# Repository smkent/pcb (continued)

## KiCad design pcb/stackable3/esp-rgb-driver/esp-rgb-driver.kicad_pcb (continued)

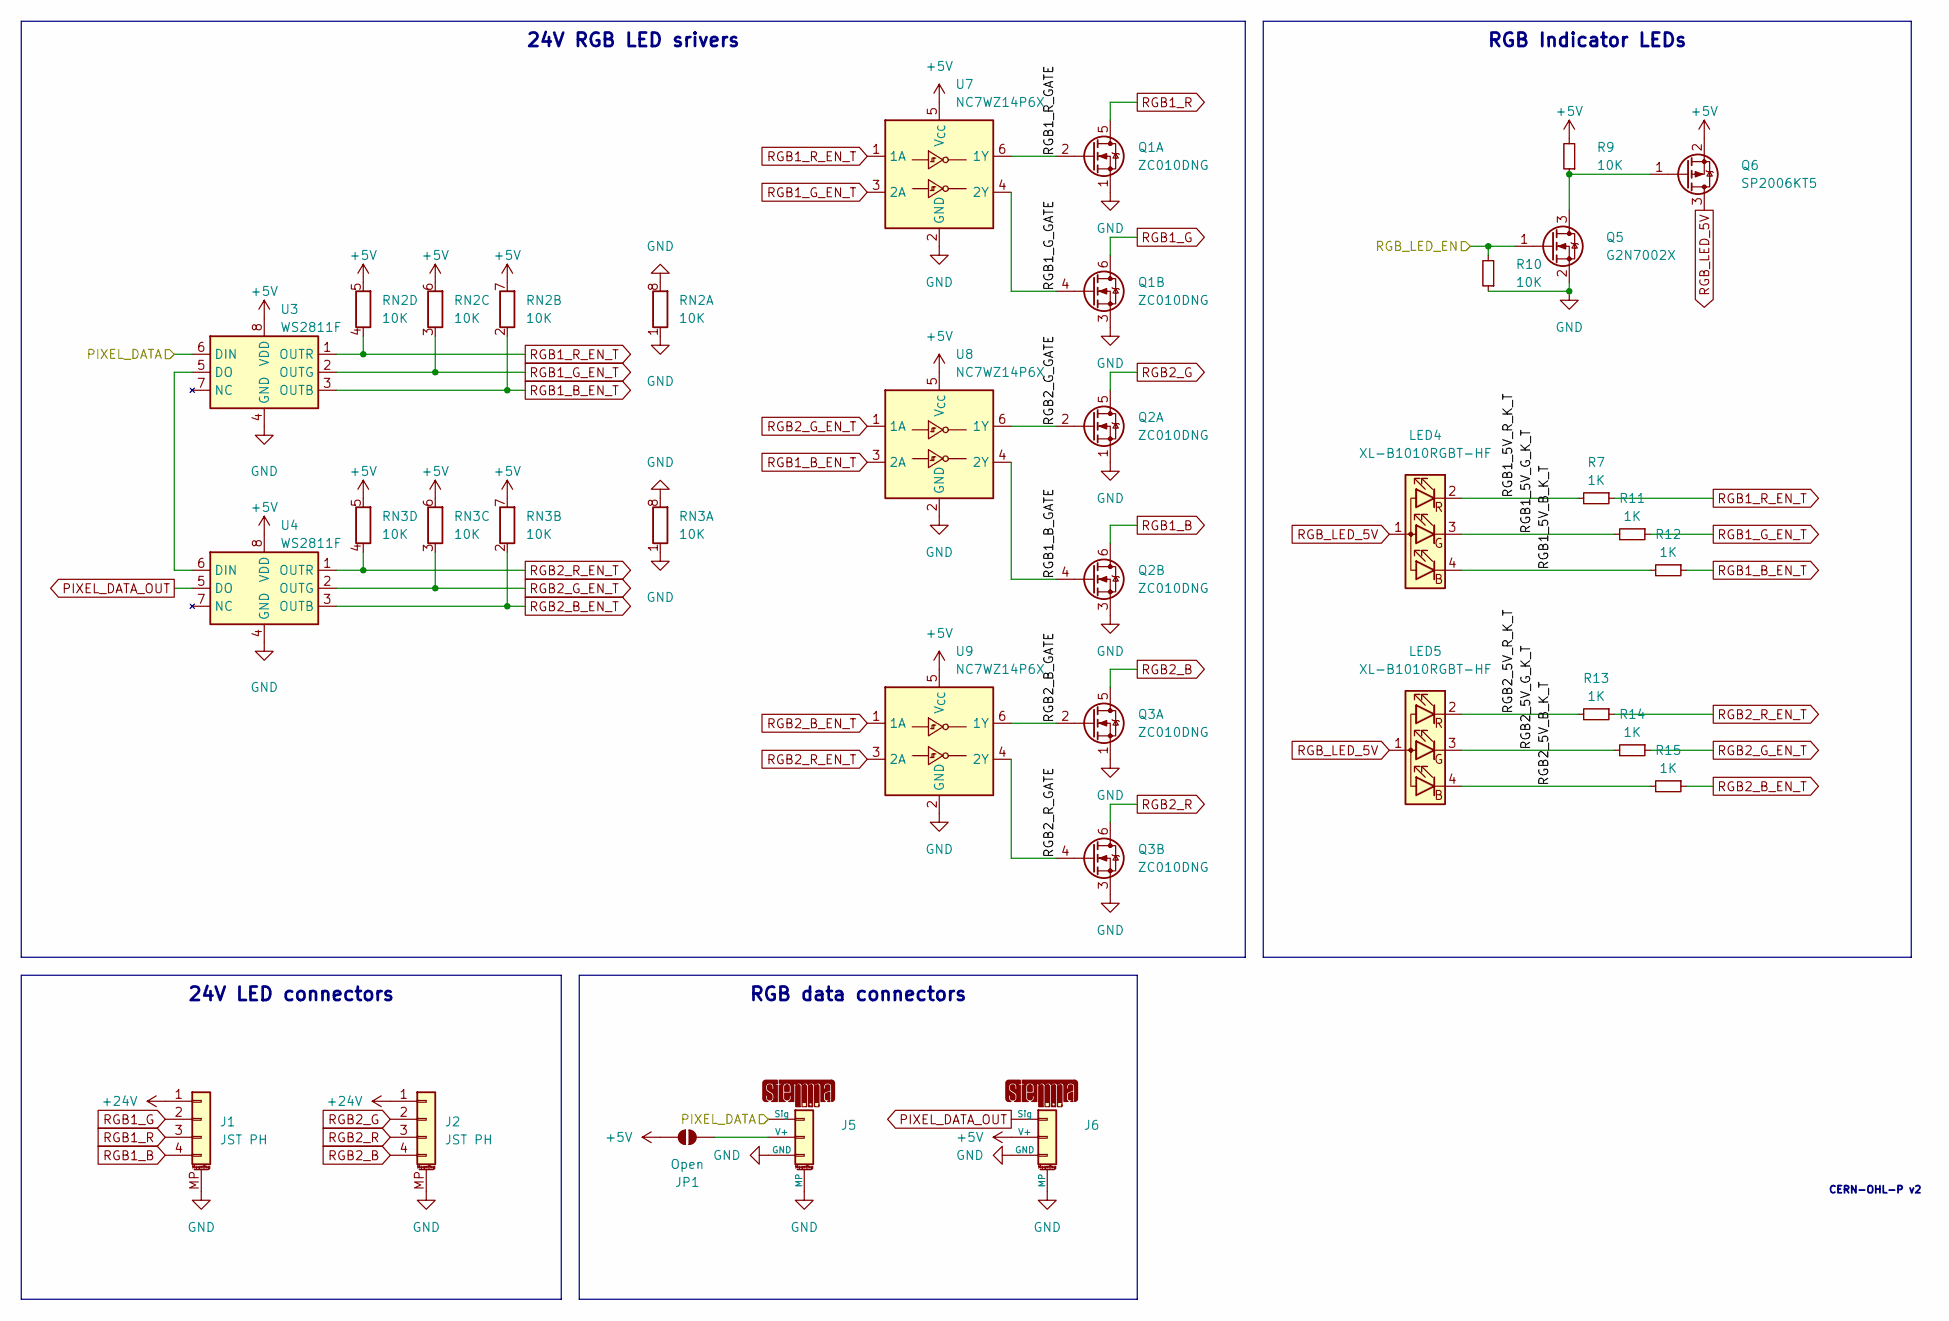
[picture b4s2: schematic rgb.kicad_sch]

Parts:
J1, J2: JST PH; JST_PH_S4B-PH-SM4-TB_1x04-1MP_P2.00mm_Horizontal; LCSC Part C5343396
J5, J6: STEMMA-Signal; STEMMA-Signal-SMD-horizontal; LCSC Part C5372880
JP1: Open; SolderJumper-2_P1.3mm_Open_TrianglePad1.0x1.5mm
LED4, LED5: XL-B1010RGBT-HF; LED_RGB_XL-B1010RGBT-HF_1.0x1.0mm; LCSC Part C22464515
Q1, Q2, Q3: ZC010DNG; PDFN-8_L3.2-W3.1-P0.65-LS3.4-BL-EP2; LCSC Part C36499170
Q5: G2N7002X; SOT-523; LCSC Part C5258971
Q6: SP2006KT5; SOT-523; LCSC Part C41355141
R7, R11, R12, R13, R14, R15: 1K; R_0402_1005Metric
R9, R10: 10K; R_0402_1005Metric
RN2, RN3: 10K; R_Array_Convex_4x0603
U3, U4: WS2811F; FSOP-8_3.3x1.7mm_P0.80mm; LCSC Part C5446692
U7, U8, U9: NC7WZ14P6X; SOT-363_SC-70-6; LCSC Part C5207816

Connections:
+5V: J6.2 (V+), JP1.1 (A), Q6.2 (S), R9.2, RN2.5 (R4.2), RN2.6 (R3.2), RN2.7 (R2.2), RN3.5 (R4.2), RN3.6 (R3.2), RN3.7 (R2.2), U3.8 (VDD), U4.8 (VDD), U7.5 (V_{CC}), U8.5 (V_{CC}), U9.5 (V_{CC}); also elsewhere on the board
+24V: J1.1, J2.1; also elsewhere on the board
/RGB/RGB1_5V_B_K_T: LED4.4 (BK), R12.2
/RGB/RGB1_5V_G_K_T: LED4.3 (GK), R11.2
/RGB/RGB1_5V_R_K_T: LED4.2 (RK), R7.2
/RGB/RGB1_B_GATE: Q2.4 (G), U8.4 (2Y)
/RGB/RGB1_G_GATE: Q1.4 (G), U7.4 (2Y)
/RGB/RGB1_R_GATE: Q1.2 (G), U7.6 (1Y)
/RGB/RGB2_5V_B_K_T: LED5.4 (BK), R15.2
/RGB/RGB2_5V_G_K_T: LED5.3 (GK), R14.2
/RGB/RGB2_5V_R_K_T: LED5.2 (RK), R13.2
/RGB/RGB2_B_GATE: Q3.2 (G), U9.6 (1Y)
/RGB/RGB2_G_GATE: Q2.2 (G), U8.6 (1Y)
/RGB/RGB2_R_GATE: Q3.4 (G), U9.4 (2Y)
GND: J1.MP (MountPin), J2.MP (MountPin), J5.3 (GND), J5.MP, J6.3 (GND), J6.MP, Q1.1 (S), Q1.3 (S), Q2.1 (S), Q2.3 (S), Q3.1 (S), Q3.3 (S), Q5.2 (S), R10.1, RN2.1 (R1.1), RN2.8 (R1.2), RN3.1 (R1.1), RN3.8 (R1.2), U3.4 (GND), U4.4 (GND), U7.2 (GND), U8.2 (GND), U9.2 (GND); also elsewhere on the board
unnamed: J5.2 (V+), JP1.2 (B)
unnamed: Q5.3 (D), Q6.1 (G), R9.1
unnamed: U3.5 (DO), U4.6 (DIN)
PIXEL_DATA: J5.1 (Sig), U3.6 (DIN); also elsewhere on the board
PIXEL_DATA_OUT: J6.1 (Sig), U4.5 (DO)
RGB1_B: J1.4, Q2.6 (D)
RGB1_B_EN_T: R12.1, RN2.2 (R2.1), U3.3 (OUTB), U8.3 (2A)
RGB1_G: J1.2, Q1.6 (D)
RGB1_G_EN_T: R11.1, RN2.3 (R3.1), U3.2 (OUTG), U7.3 (2A)
RGB1_R: J1.3, Q1.5 (D)
RGB1_R_EN_T: R7.1, RN2.4 (R4.1), U3.1 (OUTR), U7.1 (1A)
RGB2_B: J2.4, Q3.5 (D)
RGB2_B_EN_T: R15.1, RN3.2 (R2.1), U4.3 (OUTB), U9.1 (1A)
RGB2_G: J2.2, Q2.5 (D)
RGB2_G_EN_T: R14.1, RN3.3 (R3.1), U4.2 (OUTG), U8.1 (1A)
RGB2_R: J2.3, Q3.6 (D)
RGB2_R_EN_T: R13.1, RN3.4 (R4.1), U4.1 (OUTR), U9.3 (2A)
RGB_LED_5V: LED4.1 (A), LED5.1 (A), Q6.3 (D)
RGB_LED_EN: Q5.1 (G), R10.2; also elsewhere on the board

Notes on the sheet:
24V LED connectors
RGB Indicator LEDs
24V RGB LED srivers
RGB data connectors
CERN-OHL-P v2

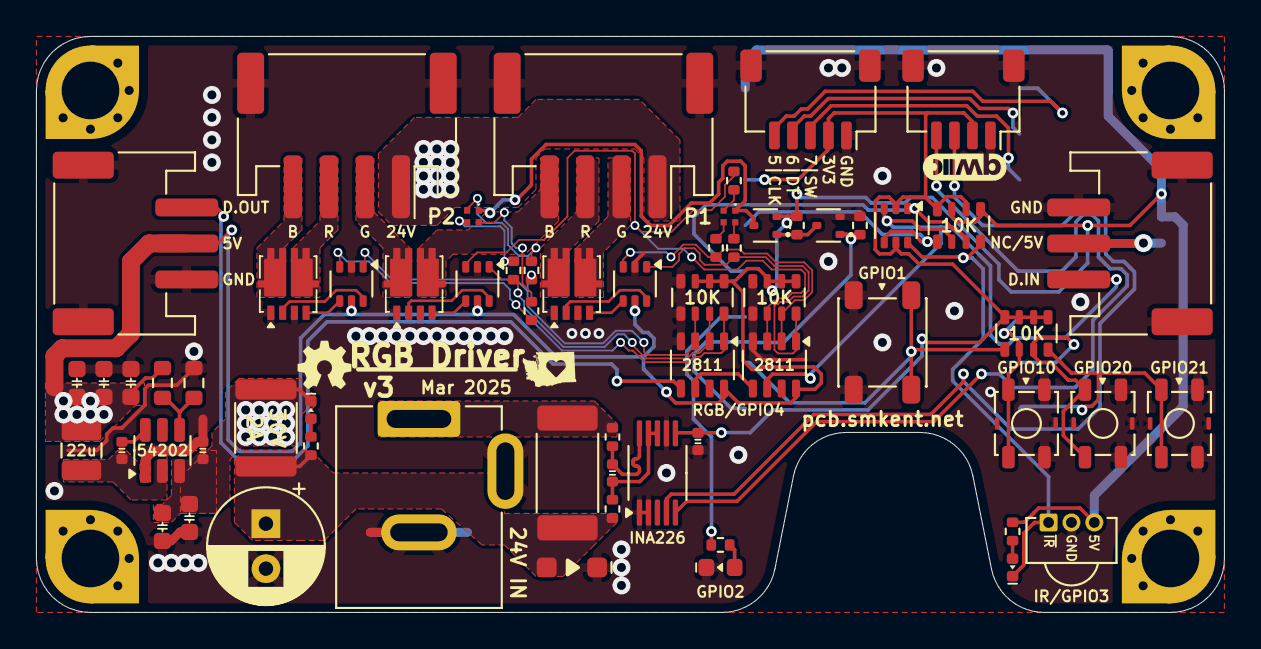
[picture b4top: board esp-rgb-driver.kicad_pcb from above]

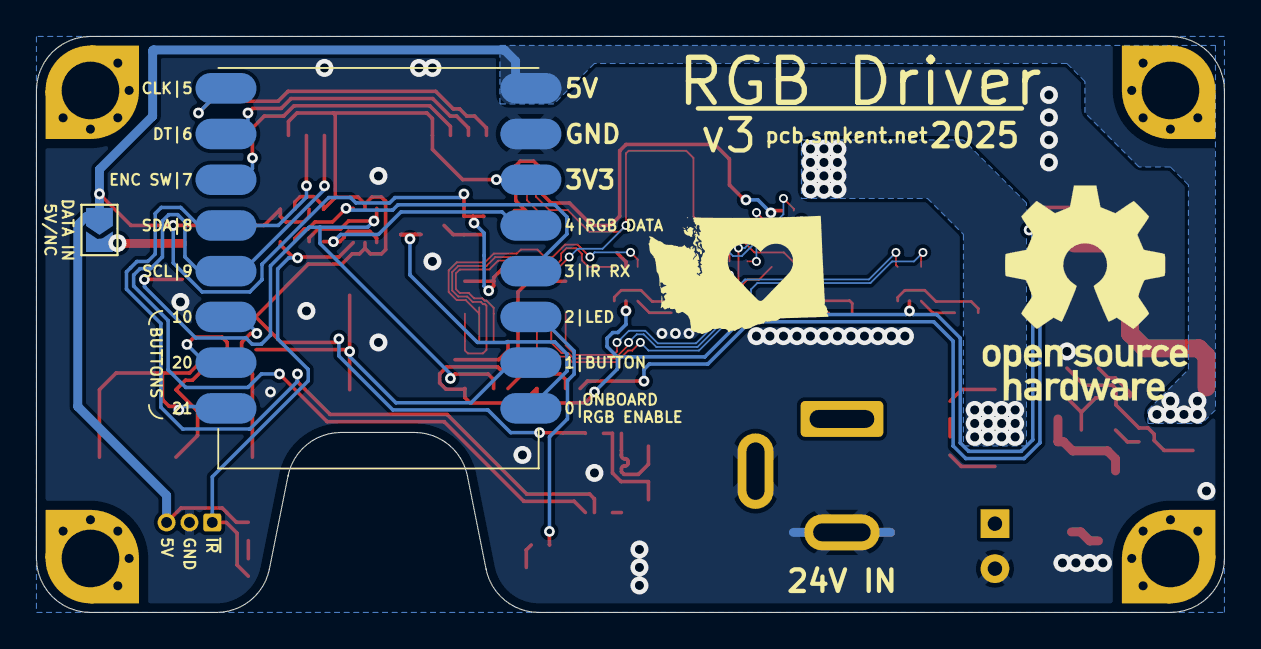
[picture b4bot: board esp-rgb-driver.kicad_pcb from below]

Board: 2 copper layers, 66.0 x 32.0 mm, 65 parts (2 on the bottom side), 58 nets.

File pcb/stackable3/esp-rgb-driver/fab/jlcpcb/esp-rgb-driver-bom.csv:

Comment,Designator,Footprint,LCSC
SN74LVC1T45Z6,"U2,U6",Package_TO_SOT_SMD:SOT-563,C441819
10K,RN1,discrete:R_Array_Convex_4x0603_HandSolder,C110924
30V 2A,F1,Fuse:Fuse_1812_4532Metric,C22366122
DC-005,J0,connector:BarrelJack_DC-005_THT_Horizontal,
13K,R2,Resistor_SMD:R_0603_1608Metric,C22797
22u,"C5,C6,C7",discrete:C_0603_1608Metric,
5K1,"R3,R6",Resistor_SMD:R_0402_1005Metric,
JST PH,"J1,J2",connector:JST_PH_S4B-PH-SM4-TB_1x04-1MP_P2.00mm_Horizontal,C5343396
STEMMA-Signal,"J5,J6",connector:STEMMA-Signal-SMD-horizontal,C5372880
ZC010DNG,"Q1,Q2,Q3",package:PDFN-8_L3.2-W3.1-P0.65-LS3.4-BL-EP2,C36499170
Ice Blue,LED1,discrete:LED_0603_1608Metric,
22u,L1,discrete:L_Power_7.0x6.6mm_0630,
NC7WZ14P6X,"U7,U8,U9",package:SOT-363_SC-70-6_HandSolder,C5207816
Red,LED2,discrete:LED_0402_1005Metric,
Pink,LED3,discrete:LED_0402_1005Metric,
Qwiic,J8,connector:Qwiic-SMD-horizontal-logo-bottom-pinout,C19270571
~,SM1,module:ESP32-C3-Super-Mini-Castellated-SMD,
JST SH,J3,connector:JST_SH_SM05B-SRSS-TB_1x05-1MP_P1.00mm_Horizontal,C7433426
10u,"C1,C2",discrete:C_0603_1608Metric,
100K,R1,Resistor_SMD:R_0603_1608Metric,
3.3mm,"SW2,SW3,SW4,SW5",electromechanical:SW_Push_1P1T_NO_3.3x3.3mm_MP,
0u1,"C3,C4",discrete:C_0402_1005Metric,
IRM,U5,package:IRM_5.0x5.0mm_SIP-3_P1.27mm_THT,C7433078
10K,"R5,R7",Resistor_SMD:R_0402_1005Metric,
1K,R4,Resistor_SMD:R_0402_1005Metric,
D_TVS,D1,package:D_SOD-123F,C7473232
470u,C0,Capacitor_SMD:CP_Elec_8x10,C7471889
SW_Push,SW1,Button_Switch_SMD:SW_SPST_PTS647_Sx50,C22459537
TPS54202DDCR,U1,Package_TO_SOT_SMD:SOT-23-6,C191884
WS2811F,"U3,U4",package:FSOP-8_3.3x1.7mm_P0.80mm,C5446692

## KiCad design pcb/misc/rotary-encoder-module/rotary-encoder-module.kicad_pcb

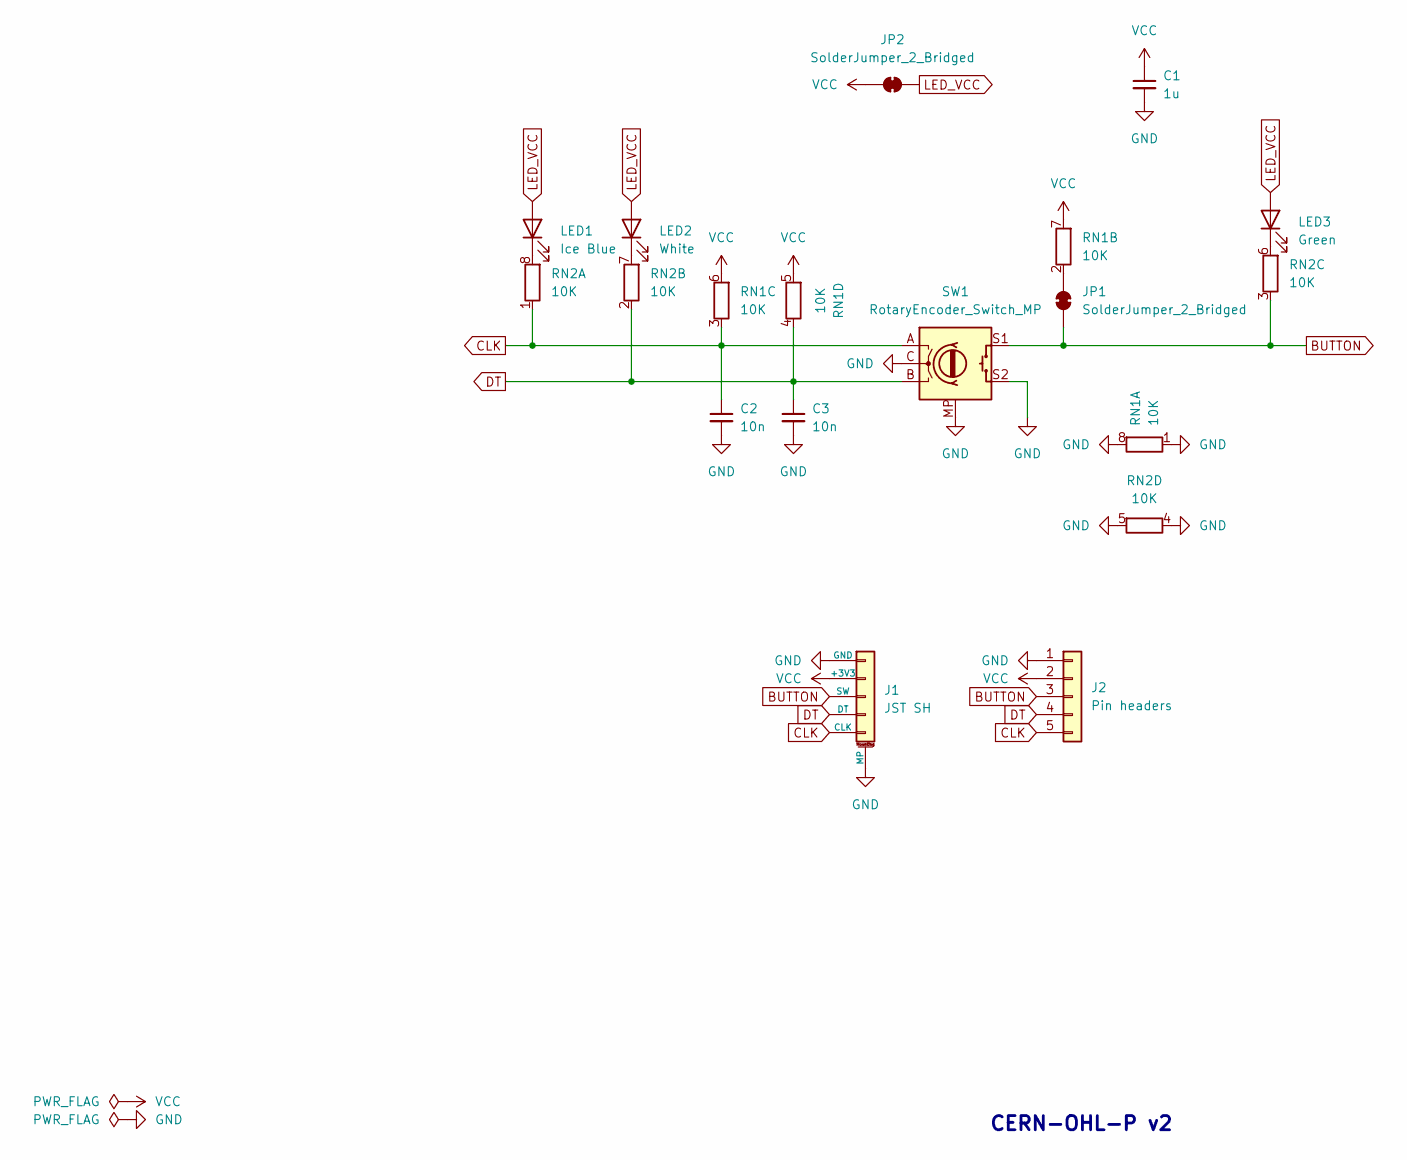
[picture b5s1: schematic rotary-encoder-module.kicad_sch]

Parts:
C1: 1u; C_0603_1608Metric_Pad1.08x0.95mm_HandSolder; LCSC Part C5199872
C2, C3: 10n; C_0603_1608Metric_Pad1.08x0.95mm_HandSolder; LCSC Part C1589
J1: JST SH; JST_SH_SM05B-SRSS-TB_1x05-1MP_P1.00mm_Horizontal; LCSC Part C7433426
J2: Pin headers; PinHeader_1x05_P2.54mm_Vertical_simple_pad1gnd
JP1, JP2: SolderJumper_2_Bridged; SolderJumper-2_P1.3mm_Bridged_RoundedPad1.0x1.5mm
LED1: Ice Blue; LED_0402_1005Metric_Pad0.77x0.64mm_HandSolder; LCSC Part C7496805
LED2: White; LED_0402_1005Metric_Pad0.77x0.64mm_HandSolder; LCSC Part C20613596
LED3: Green; LED_0402_1005Metric_Pad0.77x0.64mm_HandSolder; LCSC Part C7496801
RN1, RN2: 10K; R_Array_Convex_4x0603; LCSC Part C110924
SW1: RotaryEncoder_Switch_MP; RotaryEncoder_Alps_EC11E-Switch_Vertical_H20mm

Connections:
BUTTON: J1.3 (SW), J2.3, JP1.1 (A), RN2.3 (R3.1), SW1.S1
CLK: C2.1, J1.5 (CLK), J2.5, RN1.3 (R3.1), RN2.1 (R1.1), SW1.A
DT: C3.1, J1.4 (DT), J2.4, RN1.4 (R4.1), RN2.2 (R2.1), SW1.B
GND: C1.2, C2.2, C3.2, J1.1 (GND), J1.MP, J2.1, RN1.1 (R1.1), RN1.8 (R1.2), RN2.4 (R4.1), RN2.5 (R4.2), SW1.C, SW1.MP, SW1.S2
LED_VCC: JP2.2 (B), LED1.2 (A), LED2.2 (A), LED3.2 (A)
unnamed: JP1.2 (B), RN1.2 (R2.1)
unnamed: LED1.1 (K), RN2.8 (R1.2)
unnamed: LED2.1 (K), RN2.7 (R2.2)
unnamed: LED3.1 (K), RN2.6 (R3.2)
VCC: C1.1, J1.2 (+3V3), J2.2, JP2.1 (A), RN1.5 (R4.2), RN1.6 (R3.2), RN1.7 (R2.2)

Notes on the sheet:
CERN-OHL-P v2

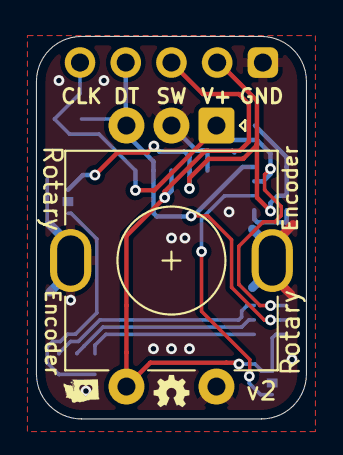
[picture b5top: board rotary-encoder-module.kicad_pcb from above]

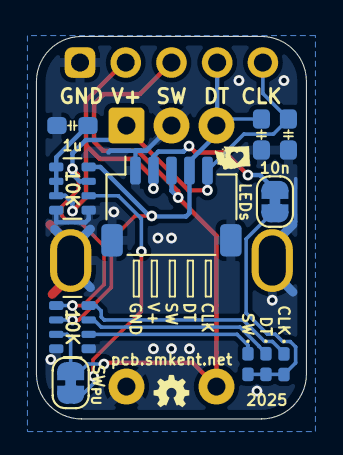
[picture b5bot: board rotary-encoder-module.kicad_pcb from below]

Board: 2 copper layers, 15.0 x 21.2 mm, 13 parts (12 on the bottom side), 10 nets.

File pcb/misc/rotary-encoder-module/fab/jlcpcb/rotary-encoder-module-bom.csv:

Comment,Designator,Footprint,LCSC
Green,LED3,LED_SMD:LED_0402_1005Metric_Pad0.77x0.64mm_HandSolder,C7496801
RotaryEncoder_Switch_MP,SW1,electromechanical:RotaryEncoder_Alps_EC11E-Switch_Vertical_H20mm,
Ice Blue,LED1,LED_SMD:LED_0402_1005Metric_Pad0.77x0.64mm_HandSolder,C7496805
White,LED2,LED_SMD:LED_0402_1005Metric_Pad0.77x0.64mm_HandSolder,C20613596
10K,"RN1,RN2",discrete:R_Array_Convex_4x0603,C110924
JST SH,J1,connector:JST_SH_SM05B-SRSS-TB_1x05-1MP_P1.00mm_Horizontal,C7433426
10n,"C2,C3",discrete:C_0603_1608Metric_Pad1.08x0.95mm_HandSolder,C1589
Pin headers,J2,custom:PinHeader_1x05_P2.54mm_Vertical_simple_pad1gnd,
1u,C1,discrete:C_0603_1608Metric_Pad1.08x0.95mm_HandSolder,C5199872

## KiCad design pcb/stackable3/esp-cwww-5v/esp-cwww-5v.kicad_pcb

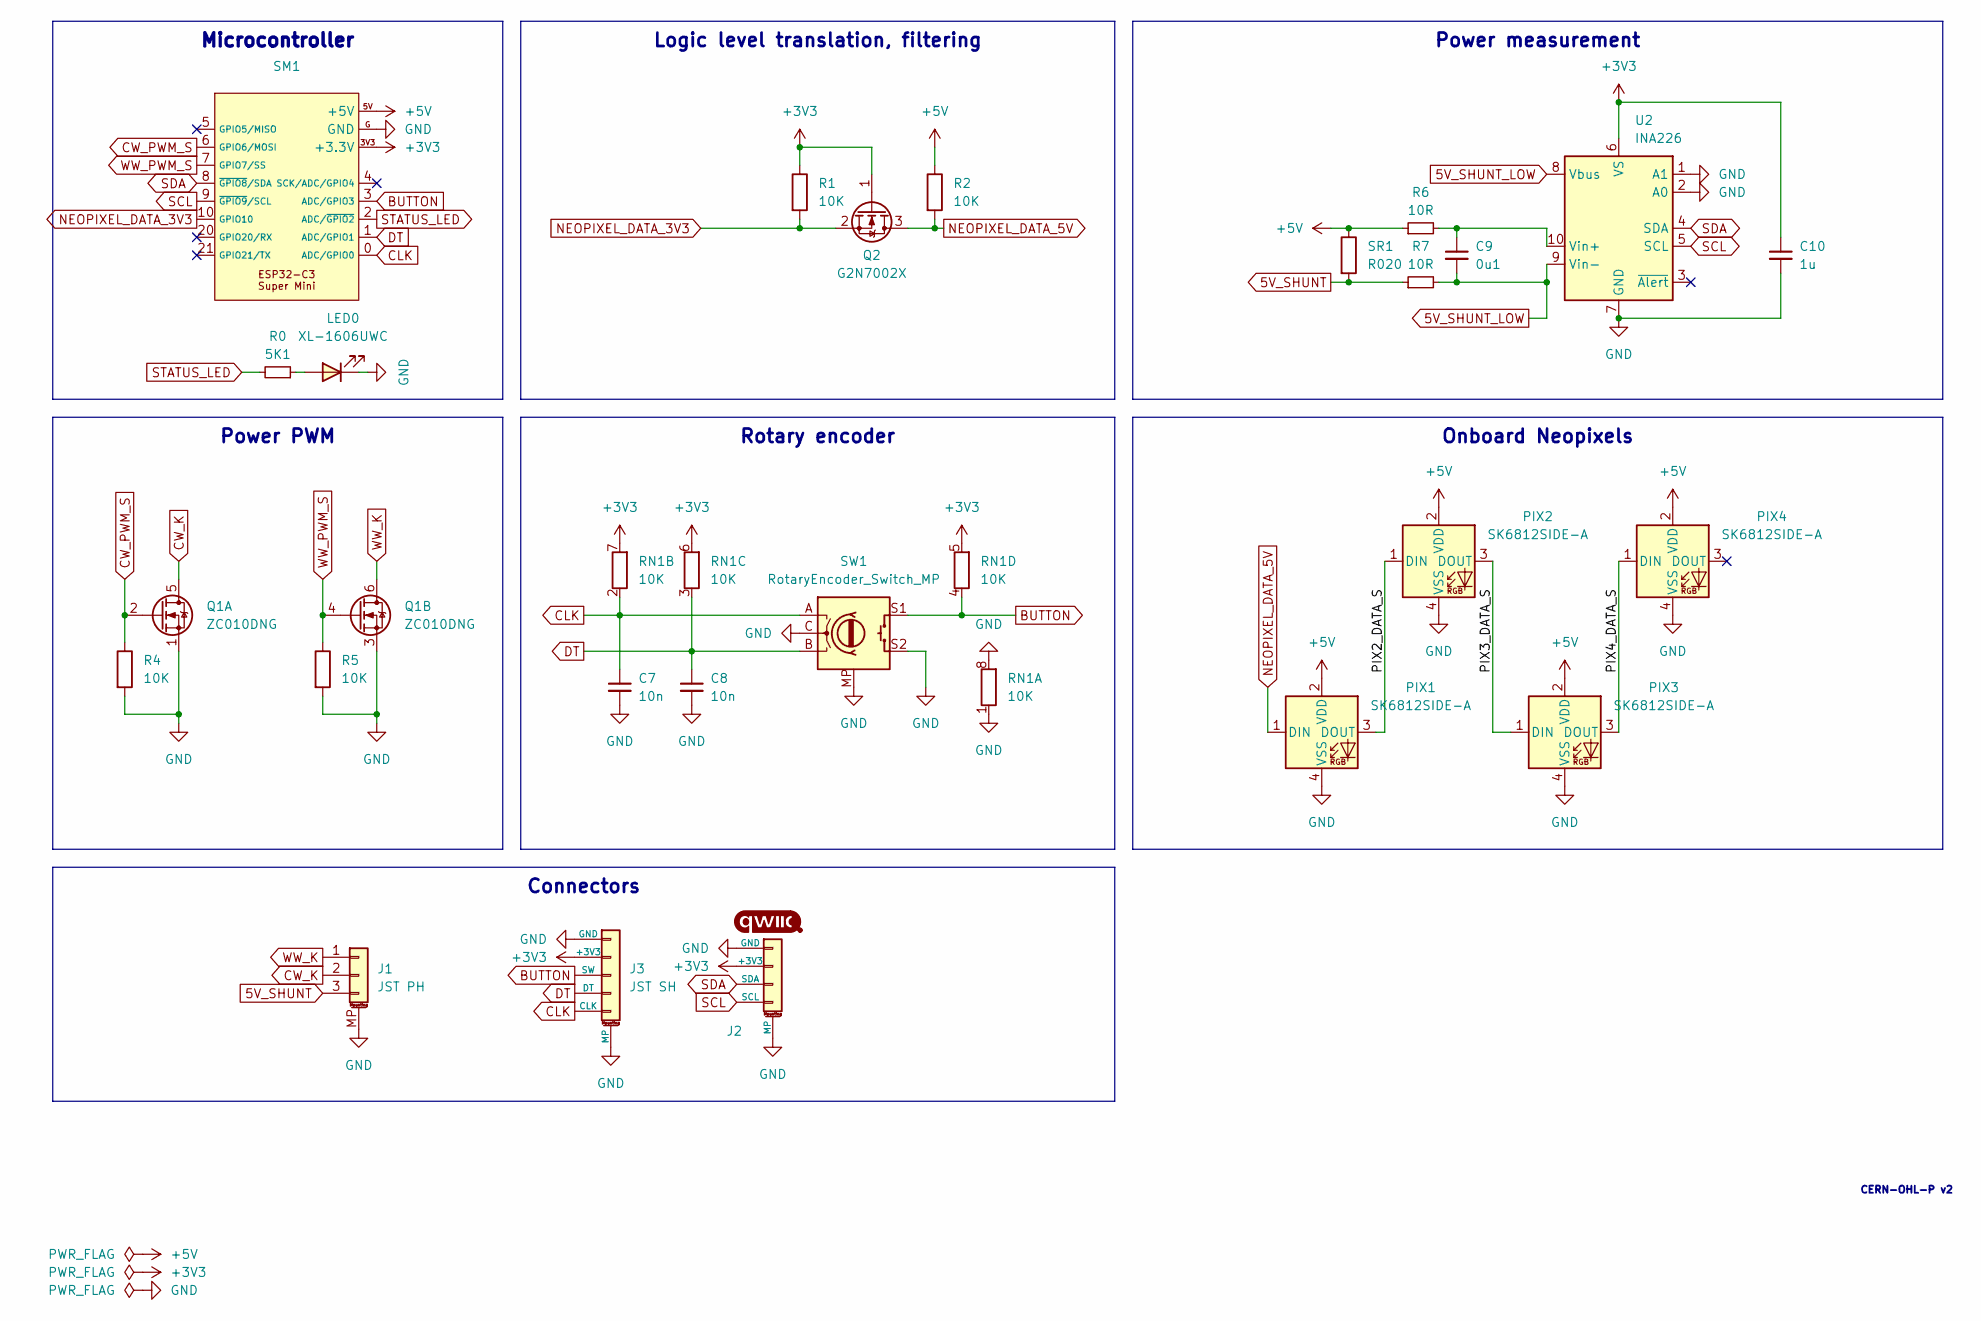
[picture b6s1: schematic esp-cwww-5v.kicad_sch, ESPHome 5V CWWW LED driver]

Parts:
C7, C8: 10n; C_0402_1005Metric; LCSC Part C60133
C9: 0u1; C_0402_1005Metric; LCSC Part C152814
C10: 1u; C_0402_1005Metric; LCSC Part C52923
J1: JST PH; STEMMA-Signal-SMD-horizontal; LCSC Part C5372880
J2: Qwiic; Qwiic-SMD-horizontal; LCSC Part C19270571
J3: JST SH; JST_SH_SM05B-SRSS-TB_1x05-1MP_P1.00mm_Horizontal; LCSC Part C7433426
LED0: XL-1606UWC; LED_SideEmitter_1.7x1.1mm; LCSC Part C965866
PIX1, PIX2, PIX3, PIX4: SK6812SIDE-A; LED_SK6812SIDE-A_4.0x1.6mm; LCSC Part C2890037
Q1: ZC010DNG; PDFN-8_L3.2-W3.1-P0.65-LS3.4-BL-EP2; LCSC Part C36499170
Q2: G2N7002X; SOT-523; LCSC Part C5258971
R0: 5K1; R_0402_1005Metric; LCSC Part C25905
R1, R2, R4, R5: 10K; R_0402_1005Metric; LCSC Part C25744
R6, R7: 10R; R_0402_1005Metric; LCSC Part C25077
RN1: 10K; R_Array_Convex_4x0402; LCSC Part C7422173
SM1: ESP32-C3-Super-Mini-Pins
SR1: R020; R_2512_6332Metric_Pad1.40x3.35mm_HandSolder; LCSC Part C5375467
SW1: RotaryEncoder_Switch_MP; RotaryEncoder_Alps_EC11-Switch_Horizontal_H20mm
U2: INA226; VSSOP-10_3x3mm_P0.5mm; LCSC Part C49851

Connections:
5V_SHUNT: J1.3, R7.1, SR1.2
5V_SHUNT_LOW: C9.2, R7.2, U2.8 (Vbus), U2.9 (Vin-)
+3V3: C10.1, J2.2 (+3V3), J3.2 (+3V3), Q2.1 (G), R1.1, RN1.5 (R4.2), RN1.6 (R3.2), RN1.7 (R2.2), SM1.3V3 (+3.3V), U2.6 (VS)
+5V: PIX1.2 (VDD), PIX2.2 (VDD), PIX3.2 (VDD), PIX4.2 (VDD), R2.1, R6.1, SM1.5V (+5V), SR1.1
/PIX2_DATA_S: PIX1.3 (DOUT), PIX2.1 (DIN)
/PIX3_DATA_S: PIX2.3 (DOUT), PIX3.1 (DIN)
/PIX4_DATA_S: PIX3.3 (DOUT), PIX4.1 (DIN)
BUTTON: J3.3 (SW), RN1.4 (R4.1), SM1.3 (ADC/GPIO3), SW1.S1
CLK: C7.1, J3.5 (CLK), RN1.2 (R2.1), SM1.0 (ADC/GPIO0), SW1.A
CW_K: J1.2, Q1.5 (D)
CW_PWM_S: Q1.2 (G), R4.1, SM1.6 (GPIO6/MOSI)
DT: C8.1, J3.4 (DT), RN1.3 (R3.1), SM1.1 (ADC/GPIO1), SW1.B
GND: C7.2, C8.2, C10.2, J1.MP (MountPin), J2.1 (GND), J2.MP, J3.1 (GND), J3.MP, LED0.1 (K), PIX1.4 (VSS), PIX2.4 (VSS), PIX3.4 (VSS), PIX4.4 (VSS), Q1.1 (S), Q1.3 (S), R4.2, R5.2, RN1.1 (R1.1), RN1.8 (R1.2), SM1.G (GND), SW1.C, SW1.MP, SW1.S2, U2.1 (A1), U2.2 (A0), U2.7 (GND)
NEOPIXEL_DATA_3V3: Q2.2 (S), R1.2, SM1.10 (GPIO10)
NEOPIXEL_DATA_5V: PIX1.1 (DIN), Q2.3 (D), R2.2
unnamed: LED0.2 (A), R0.1
unnamed: C9.1, R6.2, U2.10 (Vin+)
SCL: J2.4 (SCL), SM1.9 (~GPIO9/SCL), U2.5 (SCL)
SDA: J2.3 (SDA), SM1.8 (~GPIO8/SDA), U2.4 (SDA)
STATUS_LED: R0.2, SM1.2 (ADC/~GPIO2)
WW_K: J1.1, Q1.6 (D)
WW_PWM_S: Q1.4 (G), R5.1, SM1.7 (GPIO7/SS)

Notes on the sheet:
Onboard Neopixels
Logic level translation, filtering
Connectors
Power PWM
Power measurement
Rotary encoder
Microcontroller
CERN-OHL-P v2

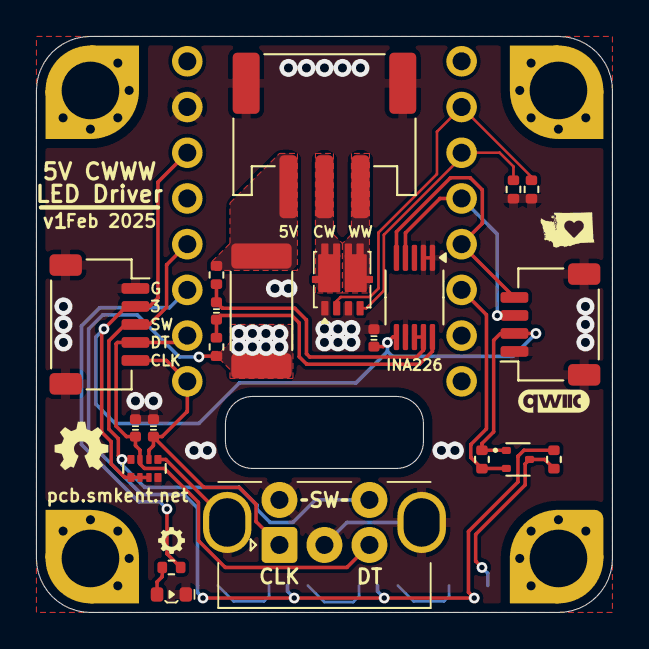
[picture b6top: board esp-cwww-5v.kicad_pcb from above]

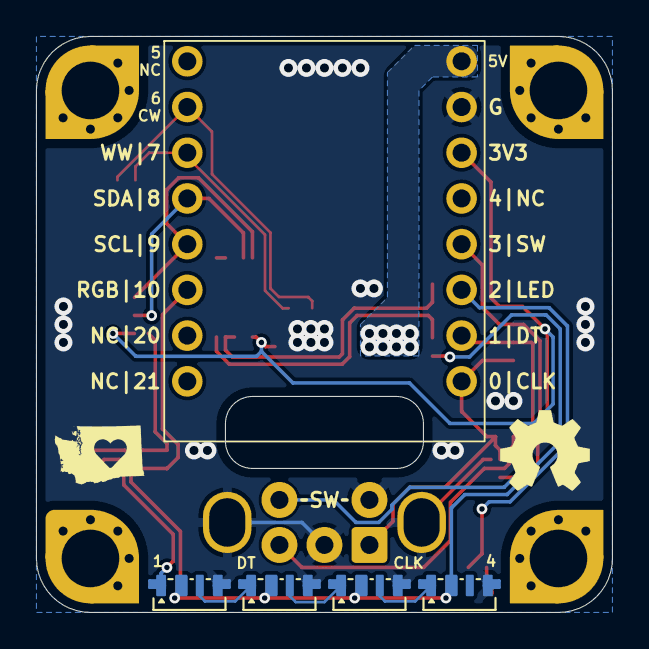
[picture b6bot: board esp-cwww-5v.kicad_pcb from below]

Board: 2 copper layers, 32.0 x 32.0 mm, 26 parts (5 on the bottom side), 22 nets.

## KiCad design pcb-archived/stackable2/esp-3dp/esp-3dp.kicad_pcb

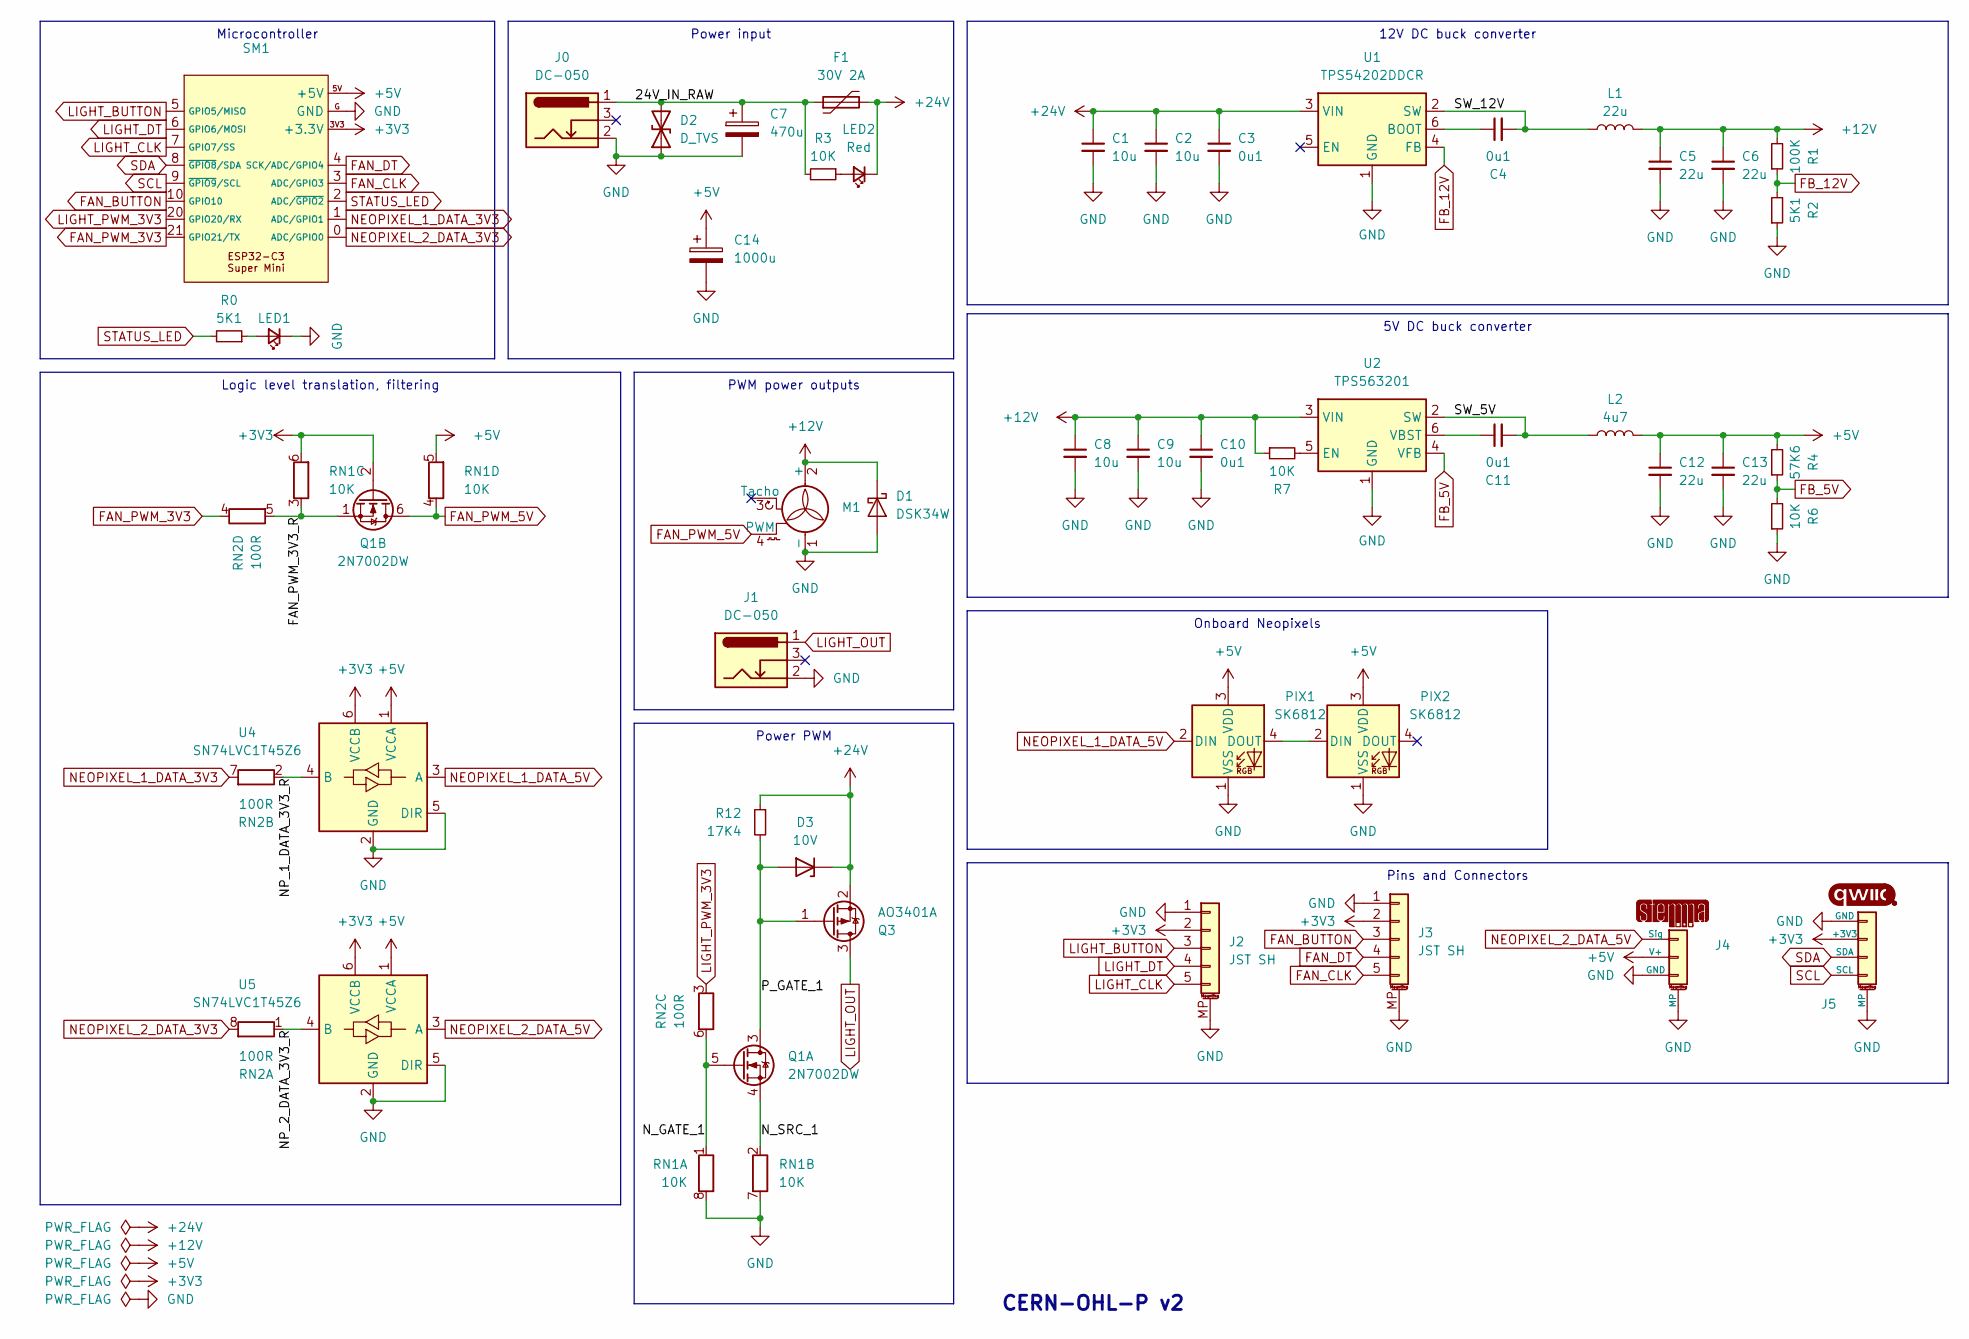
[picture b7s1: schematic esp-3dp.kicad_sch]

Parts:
C1, C2, C8, C9: 10u; C_0603_1608Metric
C3, C4, C10, C11: 0u1; C_0402_1005Metric
C5, C6: 22u; C_0805_2012Metric
C7: 470u; CP_Elec_8x10
C12, C13: 22u; C_0603_1608Metric
C14: 1000u; CP_Elec_8x10
D1: DSK34W; D_SOD-123F; LCSC Part C3014041
D2: D_TVS; D_SOD-123F
D3: 10V; D_SOD-523
F1: 30V 2A; Fuse_1812_4532Metric
J0, J1: DC-050; BarrelJack_DC-050_SMT_Horizontal
J2, J3: JST SH; JST_SH_SM05B-SRSS-TB_1x05-1MP_P1.00mm_Horizontal
J4: STEMMA-Signal; STEMMA-Signal-SMD-horizontal
J5: Qwiic; Qwiic-SMD-horizontal
L1: 22u; L_Power_7.0x6.6mm_0630
L2: 4u7; L_1008_2520Metric
LED1: LED_Small; LED_0603_1608Metric
LED2: Red; LED_0402_1005Metric
M1: KF2510; FanPinHeader_1x04_P2.54mm_Horizontal
PIX1, PIX2: SK6812; LED_SK6812_PLCC4_5.0x5.0mm_P3.2mm
Q1: 2N7002DW; SOT-363_SC-70-6_HandSolder; LCSC Part C5190214
Q3: AO3401A; SOT-23
R0: 5K1; R_0603_1608Metric
R1: 100K; R_0402_1005Metric
R2: 5K1; R_0402_1005Metric
R3, R6, R7: 10K; R_0402_1005Metric
R4: 57K6; R_0402_1005Metric
R12: 17K4; R_0603_1608Metric
RN1: 10K; R_Array_Convex_4x0603_HandSolder
RN2: 100R; R_Array_Convex_4x0603_HandSolder
SM1: ESP32-C3-Super-Mini-Castellated-SMD-only
U1: TPS54202DDCR; SOT-23-6; LCSC Part C191884
U2: TPS563201; SOT-23-6
U4, U5: SN74LVC1T45Z6; SOT-563; LCSC Part C441819

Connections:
+3V3: J2.2, J3.2, J5.2 (+3V3), Q1.2 (G), RN1.6 (R3.2), SM1.3V3 (+3.3V), U4.6 (VCCB), U5.6 (VCCB)
+5V: C12.1, C13.1, C14.1, J4.2 (V+), L2.2, PIX1.3 (VDD), PIX2.3 (VDD), R4.2, RN1.5 (R4.2), SM1.5V (+5V), U4.1 (VCCA), U5.1 (VCCA)
+12V: C5.1, C6.1, C8.1, C9.1, C10.1, D1.1 (K), L1.2, M1.2 (+), R1.2, R7.1, U2.3 (VIN)
+24V: C1.1, C2.1, C3.1, D3.1 (K), F1.2, LED2.1 (K), Q3.2 (S), R12.1, U1.3 (VIN)
/24V_IN_RAW: C7.1, D2.2 (A2), F1.1, J0.1, R3.2
/FAN_PWM_3V3_R: Q1.1 (S), RN1.3 (R3.1), RN2.5 (R4.2)
/NP_1_DATA_3V3_R: RN2.2 (R2.1), U4.4 (B)
/NP_2_DATA_3V3_R: RN2.1 (R1.1), U5.4 (B)
/N_GATE_1: Q1.5 (G), RN1.1 (R1.1), RN2.6 (R3.2)
/N_SRC_1: Q1.4 (S), RN1.2 (R2.1)
/P_GATE_1: D3.2 (A), Q1.3 (D), Q3.1 (G), R12.2
/SW_5V: C11.2, L2.1, U2.2 (SW)
/SW_12V: C4.2, L1.1, U1.2 (SW)
FAN_BUTTON: J3.3, SM1.10 (GPIO10)
FAN_CLK: J3.5, SM1.3 (ADC/GPIO3)
FAN_DT: J3.4, SM1.4 (SCK/ADC/GPIO4)
FAN_PWM_3V3: RN2.4 (R4.1), SM1.21 (GPIO21/TX)
FAN_PWM_5V: M1.4 (PWM), Q1.6 (D), RN1.4 (R4.1)
FB_5V: R4.1, R6.2, U2.4 (VFB)
FB_12V: R1.1, R2.2, U1.4 (FB)
GND: C1.2, C2.2, C3.2, C5.2, C6.2, C7.2, C8.2, C9.2, C10.2, C12.2, C13.2, C14.2, D1.2 (A), D2.1 (A1), J0.2, J1.2, J2.1, J2.MP (MountPin), J3.1, J3.MP (MountPin), J4.3 (GND), J4.MP, J5.1 (GND), J5.MP, LED1.1 (K), M1.1 (-), PIX1.1 (VSS), PIX2.1 (VSS), R2.1, R6.1, RN1.7 (R2.2), RN1.8 (R1.2), SM1.G (GND), U1.1 (GND), U2.1 (GND), U4.2 (GND), U4.5 (DIR), U5.2 (GND), U5.5 (DIR)
LIGHT_BUTTON: J2.3, SM1.5 (GPIO5/MISO)
LIGHT_CLK: J2.5, SM1.7 (GPIO7/SS)
LIGHT_DT: J2.4, SM1.6 (GPIO6/MOSI)
LIGHT_OUT: J1.1, Q3.3 (D)
LIGHT_PWM_3V3: RN2.3 (R3.1), SM1.20 (GPIO20/RX)
NEOPIXEL_1_DATA_3V3: RN2.7 (R2.2), SM1.1 (ADC/GPIO1)
NEOPIXEL_1_DATA_5V: PIX1.2 (DIN), U4.3 (A)
NEOPIXEL_2_DATA_3V3: RN2.8 (R1.2), SM1.0 (ADC/GPIO0)
NEOPIXEL_2_DATA_5V: J4.1 (Sig), U5.3 (A)
unnamed: LED1.2 (A), R0.1
unnamed: LED2.2 (A), R3.1
unnamed: PIX1.4 (DOUT), PIX2.2 (DIN)
unnamed: C4.1, U1.6 (BOOT)
unnamed: R7.2, U2.5 (EN)
unnamed: C11.1, U2.6 (VBST)
SCL: J5.4 (SCL), SM1.9 (~GPIO9/SCL)
SDA: J5.3 (SDA), SM1.8 (~GPIO8/SDA)
STATUS_LED: R0.2, SM1.2 (ADC/~GPIO2)

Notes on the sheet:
5V DC buck converter
Power input
12V DC buck converter
Microcontroller
PWM power outputs
Onboard Neopixels
Pins and Connectors
Logic level translation, filtering
Power PWM
CERN-OHL-P v2

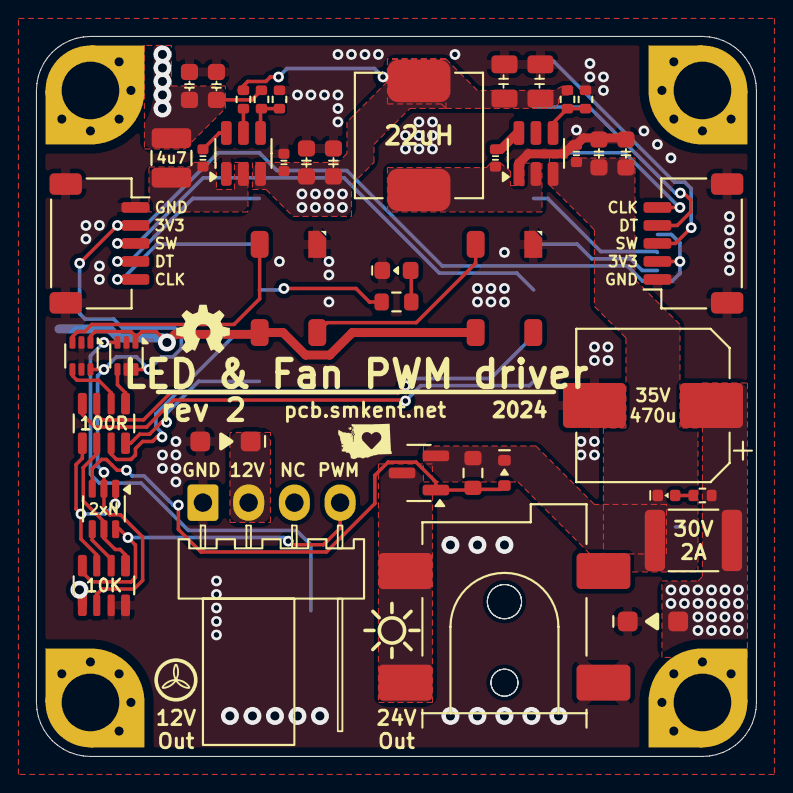
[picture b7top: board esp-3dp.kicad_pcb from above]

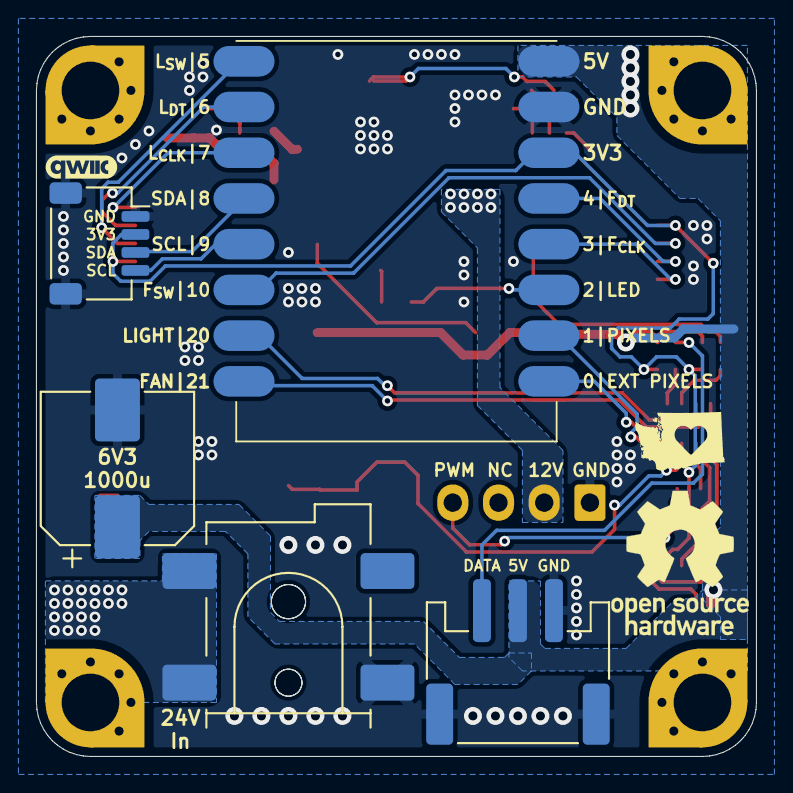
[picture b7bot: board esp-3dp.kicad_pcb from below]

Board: 2 copper layers, 40.0 x 40.0 mm, 52 parts (5 on the bottom side), 39 nets.

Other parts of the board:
MH_NE: MountingHole_3.2mm_M3_Pad_Via_corner_compact
MH_NW: MountingHole_3.2mm_M3_Pad_Via_corner_compact
MH_SE: MountingHole_3.2mm_M3_Pad_Via_corner_compact
MH_SW: MountingHole_3.2mm_M3_Pad_Via_corner_compact

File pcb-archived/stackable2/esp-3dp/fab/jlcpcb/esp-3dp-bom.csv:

Comment,Designator,Footprint,LCSC
22u,"C5,C6",passives:C_0805_2012Metric,
0u1,"C3,C4,C10,C11",passives:C_0402_1005Metric,
5K1,R0,Resistor_SMD:R_0603_1608Metric,
10V,D3,packages:D_SOD-523,
D_TVS,D2,packages:D_SOD-123F,
SN74LVC1T45DRL,"U4,U5",Package_TO_SOT_SMD:SOT-563,
17K4,R12,Resistor_SMD:R_0603_1608Metric,
100K,R1,Resistor_SMD:R_0402_1005Metric,
22u,"C12,C13",passives:C_0603_1608Metric,
DC-050,"J0,J1",custom:DC-IN_DC-050-2.0-BB_rev2,
10u,"C1,C2,C8,C9",passives:C_0603_1608Metric,
10K,"R3,R6,R7",Resistor_SMD:R_0402_1005Metric,
STEMMA-Signal,J4,connectors:STEMMA-Signal-SMD-horizontal,
4u7,L2,passives:L_1008_2520Metric,
Red,LED2,led:LED_0402_1005Metric,
~,SM1,modules:ESP32-C3-Super-Mini-Castellated-SMD-only,
DSK34W,D1,packages:D_SOD-123F,
100R,RN2,passives:R_Array_Convex_4x0603_HandSolder,
KF2510,M1,connectors:FanPinHeader_1x04_P2.54mm_Horizontal,
AO3401A,Q3,Package_TO_SOT_SMD:SOT-23,
Qwiic,J5,connectors:Qwiic-SMD-horizontal,
LED_Small,LED1,led:LED_0603_1608Metric,
TPS54202DDCR,U1,Package_TO_SOT_SMD:SOT-23-6,C191884
SK6812,"PIX1,PIX2",led:LED_SK6812_PLCC4_5.0x5.0mm_P3.2mm,
JST SH,"J2,J3",connectors:JST_SH_SM05B-SRSS-TB_1x05-1MP_P1.00mm_Horizontal,
30V 2A,F1,Fuse:Fuse_1812_4532Metric,
470u,C7,Capacitor_SMD:CP_Elec_8x10,
TPS563201,U2,Package_TO_SOT_SMD:SOT-23-6,
5K1,R2,Resistor_SMD:R_0402_1005Metric,
57K6,R4,Resistor_SMD:R_0402_1005Metric,
10K,RN1,passives:R_Array_Convex_4x0603_HandSolder,
1000u,C14,Capacitor_SMD:CP_Elec_8x10,
2N7002DW,Q1,packages:SOT-363_SC-70-6_HandSolder,C5190214
22u,L1,passives:L_Power_7.0x6.6mm_0630,
